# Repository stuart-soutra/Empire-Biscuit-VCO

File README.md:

# Empire Biscuit Voltage Controlled Oscillator
## Details
The Empire Biscuit VCO is a Eurorack Compatible 16HP module implementation of Thomas Henry's VCO design (details available here: https://www.birthofasynth.com/Thomas_Henry/Pages/VCO-1.html).
The module is a single-voice VCO with inputs for CV, Hard Sync, Exp FM, Lin FM and PWM, and sine, triangle, ramp and square wave signal outputs.
The module has controls for Fine and coarse frequency control, FM attenuation and pulse width.
## Transistor Temperature Control
Because of the temperature sensitivity of the PNP transistors (Q1 and Q2) used in the voltage-to-current convertor circuit, it is imperative that these two transistors are thermally matched as closely as possible. For this reason, I have located them as closely together as possible.
When mounting these transistors, I suggest that you apply a small amount of thermal paste between the flat signifier sides of each transistors case, then encase them in epoxy resin (and maybe cover them up with heatshrink to go full belts and braces).
## Front Panel and Mechanical Design
I have included my design of the front panel of the Empire Biscuit ("Empire-Biscuit_PANEL-DESIGN_V1.svg"), that shows mounting hole location and the graphical design - feel free to use this fully or as a drilling template (these are all in .svg format - I recommend using Inkscape to open and edit these).

I constructed the front panel out of aluminium sheet with the following specifications:
- Sheet thickness = 2mm
- Width = 80.9mm (16HP)
- Height = 128mm (Eurorack standard)

The design shows lines for the width of the (recommended) slots at each corner of the module. The end points of these line correspond to the external radius points of each slot. I went with a slot drill size of M2.5.

Other clearance hole sizes:
- Input/Output Receptacles = 8mm
- Pots = 6mm
## Current Rev (Uploaded)
Rev A
## Mods Required After Rev A Testing
As I have not yet completed the changes for Rev B, please implement the following mods if you would like to build it to (fully working) Rev B specifications:
- +12V and -12V should be swapped around at the IDC header - I accidentally mirrored the main input voltages from the power supply, so please make sure that these are the correct way around!
- All 3/4" jacks (input and output) require new connections - Pin 1 (shield) should be connected to GND, and Pin 2 should be the respective positive connection for each. The use of TRRS receptacles for mono connections caused some confusion here.
- For all potentionmeters, swap connections to pin 1 amd 3 around so that each control increases with clockwise rotation instead of decreasing.

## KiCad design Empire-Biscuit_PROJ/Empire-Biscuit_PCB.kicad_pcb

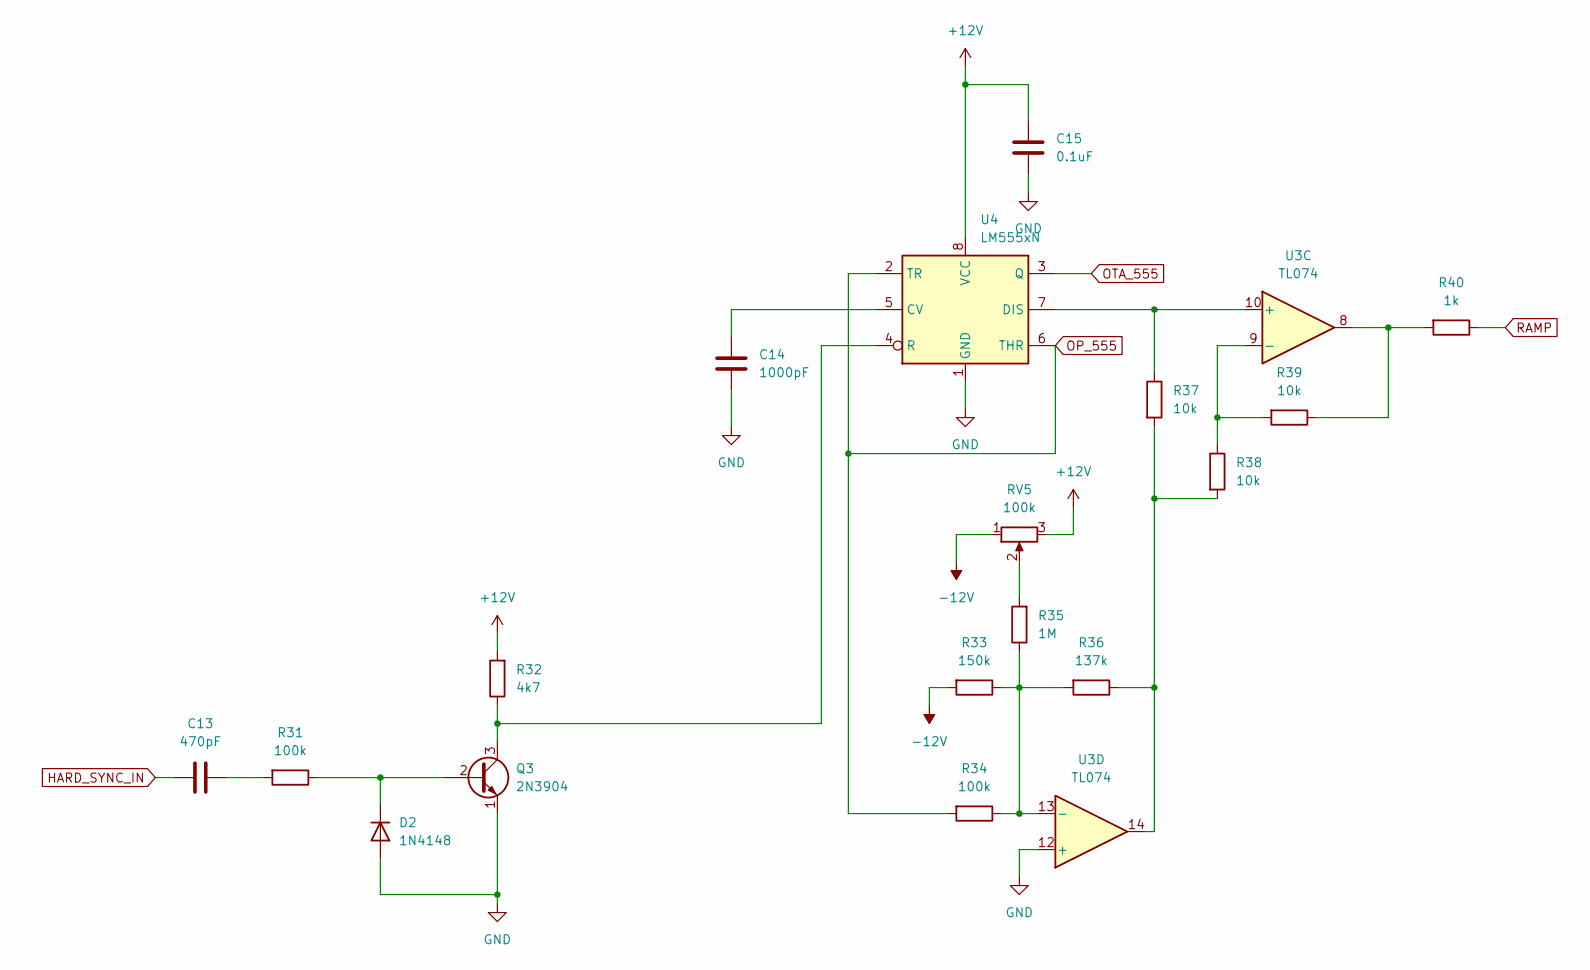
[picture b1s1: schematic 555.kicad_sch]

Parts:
C13: 470pF; C_0805_2012Metric_Pad1.18x1.45mm_HandSolder
C14: 1000pF; C_0805_2012Metric_Pad1.18x1.45mm_HandSolder
C15: 0.1uF; C_0805_2012Metric_Pad1.18x1.45mm_HandSolder
D2: 1N4148; D_DO-35_SOD27_P7.62mm_Horizontal
Q3: 2N3904; TO-92_Inline
R31, R34: 100k; R_0805_2012Metric_Pad1.20x1.40mm_HandSolder
R32: 4k7; R_0805_2012Metric_Pad1.20x1.40mm_HandSolder
R33: 150k; R_0805_2012Metric_Pad1.20x1.40mm_HandSolder
R35: 1M; R_0805_2012Metric_Pad1.20x1.40mm_HandSolder
R36: 137k; R_0805_2012Metric_Pad1.20x1.40mm_HandSolder
R37, R38, R39: 10k; R_0805_2012Metric_Pad1.20x1.40mm_HandSolder
R40: 1k; R_0805_2012Metric_Pad1.20x1.40mm_HandSolder
RV5: 100k; Potentiometer_Vishay_T73XW_Horizontal
U3: TL074
U4: LM555xN; DIP-8_W7.62mm

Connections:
+12V: C15.2, R32.2, RV5.3, U4.8 (VCC); also elsewhere on the board
-12V: R33.2, RV5.1; also elsewhere on the board
GND: C14.1, C15.1, D2.2 (A), Q3.1 (E), U3.12 (+), U4.1 (GND); also elsewhere on the board
HARD_SYNC_IN: C13.2; also elsewhere on the board
unnamed: C13.1, R31.2
unnamed: C14.2, U4.5 (CV)
unnamed: D2.1 (K), Q3.2 (B), R31.1
unnamed: Q3.3 (C), R32.1, U4.4 (R)
unnamed: R33.1, R34.1, R35.1, R36.2, U3.13 (-)
unnamed: R35.2, RV5.2
unnamed: R36.1, R37.2, R38.2, U3.14
unnamed: R37.1, U3.10 (+), U4.7 (DIS)
unnamed: R38.1, R39.2, U3.9 (-)
unnamed: R39.1, R40.2, U3.8
OP_555: R34.2, U4.2 (TR), U4.6 (THR); also elsewhere on the board
OTA_555: U4.3 (Q); also elsewhere on the board
RAMP: R40.1; also elsewhere on the board

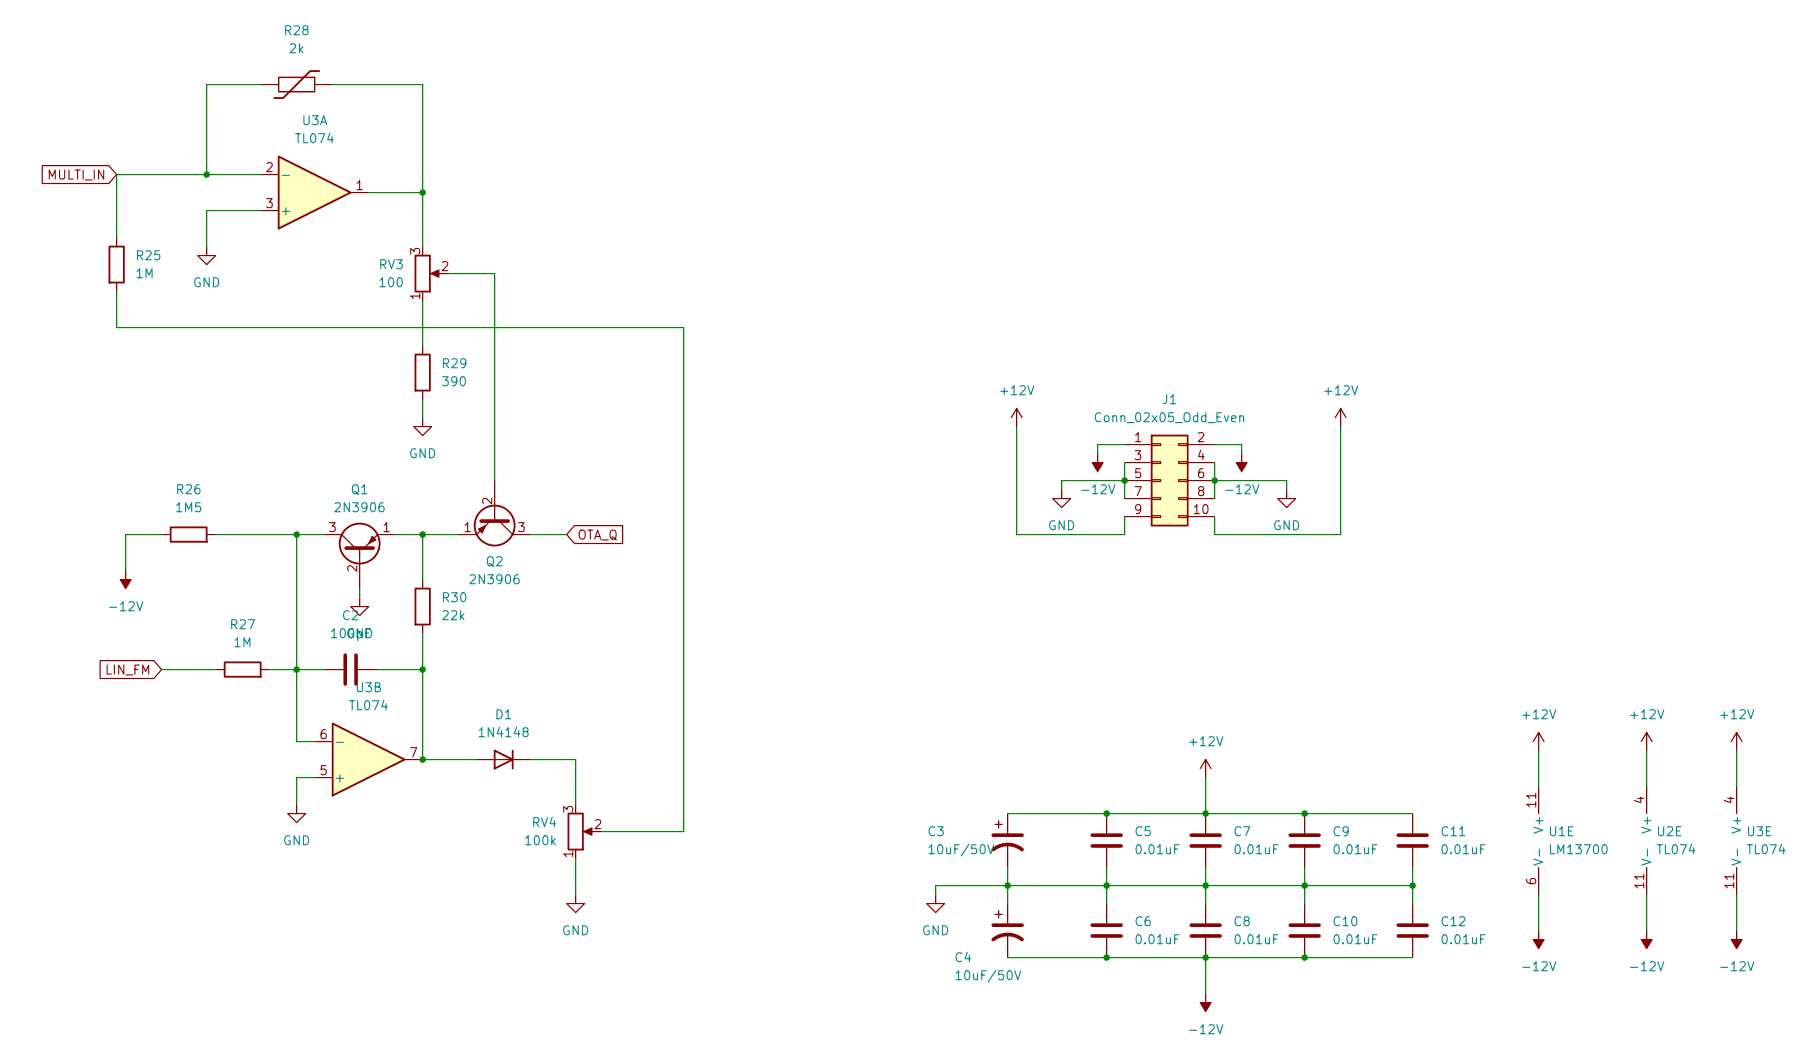
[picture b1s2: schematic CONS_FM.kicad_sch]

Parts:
C2: 100pF; C_0805_2012Metric_Pad1.18x1.45mm_HandSolder
C3, C4: 10uF/50V; CP_Radial_D5.0mm_P2.00mm
C5, C6, C7, C8, C9, C10, C11, C12: 0.01uF; C_0805_2012Metric_Pad1.18x1.45mm_HandSolder
D1: 1N4148; D_DO-35_SOD27_P7.62mm_Horizontal
J1: Conn_02x05_Odd_Even; PinHeader_2x05_P2.54mm_Vertical
Q1, Q2: 2N3906; TO-92_Inline
R25, R27: 1M; R_0805_2012Metric_Pad1.20x1.40mm_HandSolder
R26: 1M5; R_0805_2012Metric_Pad1.20x1.40mm_HandSolder
R28: 2k; R_Axial_DIN0204_L3.6mm_D1.6mm_P2.54mm_Vertical
R29: 390; R_0805_2012Metric_Pad1.20x1.40mm_HandSolder
R30: 22k; R_0805_2012Metric_Pad1.20x1.40mm_HandSolder
RV3: 100; Potentiometer_Vishay_T73XW_Horizontal
RV4: 100k; Potentiometer_Vishay_T73XW_Horizontal
U1: LM13700; SOIC-16_3.9x9.9mm_P1.27mm
U2: TL074; DIP-14_W7.62mm_Socket_LongPads
U3: TL074

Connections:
+12V: C3.1, C5.2, C7.2, C9.2, C11.2, J1.9, J1.10, U1.11 (V+), U2.4 (V+), U3.4 (V+); also elsewhere on the board
-12V: C4.2, C6.1, C8.1, C10.1, C12.1, J1.1, J1.2, R26.1, U1.6 (V-), U2.11 (V-), U3.11 (V-); also elsewhere on the board
GND: C3.2, C4.1, C5.1, C6.2, C7.1, C8.2, C9.1, C10.2, C11.1, C12.2, J1.3, J1.4, J1.5, J1.6, J1.7, J1.8, Q1.2 (B), R29.2, RV4.1, U3.3 (+), U3.5 (+); also elsewhere on the board
LIN_FM: R27.1; also elsewhere on the board
MULTI_IN: R25.1, R28.2, U3.2 (-); also elsewhere on the board
unnamed: C2.1, Q1.3 (C), R26.2, R27.2, U3.6 (-)
unnamed: C2.2, D1.2 (A), R30.2, U3.7
unnamed: D1.1 (K), RV4.3
unnamed: Q1.1 (E), Q2.1 (E), R30.1
unnamed: Q2.2 (B), RV3.2
unnamed: R25.2, RV4.2
unnamed: R28.1, RV3.3, U3.1
unnamed: R29.1, RV3.1
OTA_Q: Q2.3 (C); also elsewhere on the board

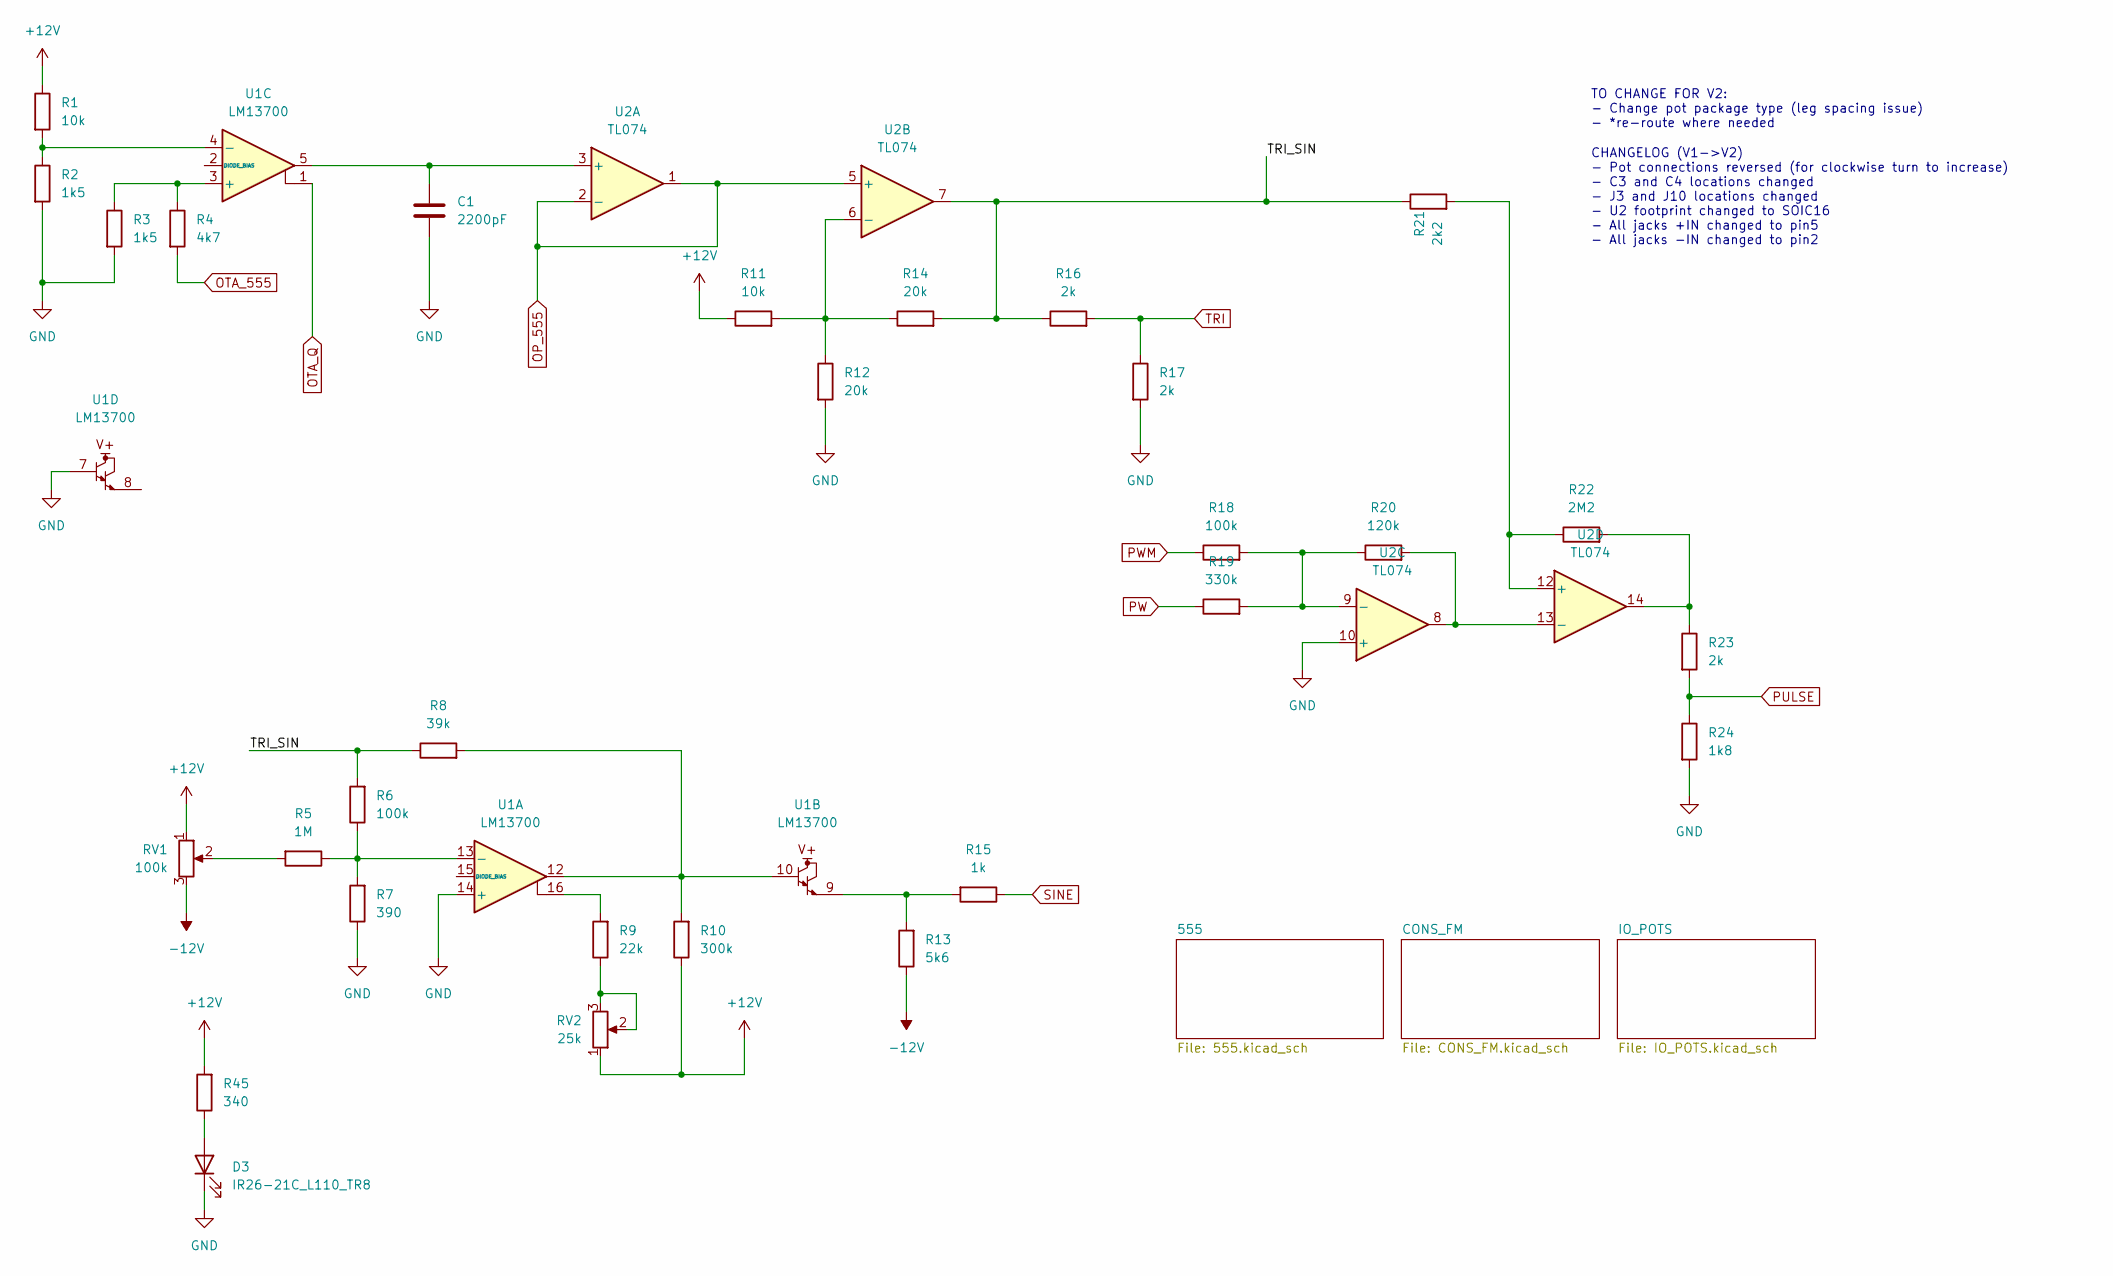
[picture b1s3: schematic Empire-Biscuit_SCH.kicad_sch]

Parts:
C1: 2200pF; C_0805_2012Metric_Pad1.18x1.45mm_HandSolder
D3: IR26-21C_L110_TR8; LED_1206_3216Metric
R1, R11: 10k; R_0805_2012Metric_Pad1.20x1.40mm_HandSolder
R2, R3: 1k5; R_0805_2012Metric_Pad1.20x1.40mm_HandSolder
R4: 4k7; R_0805_2012Metric_Pad1.20x1.40mm_HandSolder
R5: 1M; R_0805_2012Metric_Pad1.20x1.40mm_HandSolder
R6, R18: 100k; R_0805_2012Metric_Pad1.20x1.40mm_HandSolder
R7: 390; R_0805_2012Metric_Pad1.20x1.40mm_HandSolder
R8: 39k; R_0805_2012Metric_Pad1.20x1.40mm_HandSolder
R9: 22k; R_0805_2012Metric_Pad1.20x1.40mm_HandSolder
R10: 300k; R_0805_2012Metric_Pad1.20x1.40mm_HandSolder
R12, R14: 20k; R_0805_2012Metric_Pad1.20x1.40mm_HandSolder
R13: 5k6; R_0805_2012Metric_Pad1.20x1.40mm_HandSolder
R15: 1k; R_0805_2012Metric_Pad1.20x1.40mm_HandSolder
R16, R17, R23: 2k; R_0805_2012Metric_Pad1.20x1.40mm_HandSolder
R19: 330k; R_0805_2012Metric_Pad1.20x1.40mm_HandSolder
R20: 120k; R_0805_2012Metric_Pad1.20x1.40mm_HandSolder
R21: 2k2; R_0805_2012Metric_Pad1.20x1.40mm_HandSolder
R22: 2M2; R_0805_2012Metric_Pad1.20x1.40mm_HandSolder
R24: 1k8; R_0805_2012Metric_Pad1.20x1.40mm_HandSolder
R45: 340; R_0805_2012Metric_Pad1.20x1.40mm_HandSolder
RV1: 100k; Potentiometer_Vishay_T73XW_Horizontal
RV2: 25k; Potentiometer_Vishay_T73XW_Horizontal
U1: LM13700; SOIC-16_3.9x9.9mm_P1.27mm
U2: TL074; DIP-14_W7.62mm_Socket_LongPads

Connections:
+12V: R1.1, R10.1, R11.1, R45.2, RV1.1, RV2.1; also elsewhere on the board
-12V: R13.1, RV1.3; also elsewhere on the board
/TRI_SIN: R6.2, R8.1, R14.2, R16.1, R21.1, U2.7
GND: C1.2, D3.1 (K), R2.2, R3.2, R7.1, R12.2, R17.2, R24.2, U1.7, U1.14 (+), U2.10 (+); also elsewhere on the board
unnamed: C1.1, U1.5, U2.3 (+)
unnamed: D3.2 (A), R45.1
unnamed: R1.2, R2.1, U1.4 (-)
unnamed: R3.1, R4.1, U1.3 (+)
unnamed: R5.1, R6.1, R7.2, U1.13 (-)
unnamed: R5.2, RV1.2
unnamed: R9.1, RV2.2, RV2.3
unnamed: R9.2, U1.16
unnamed: R8.2, R10.2, U1.10, U1.12
unnamed: R11.2, R12.1, R14.1, U2.6 (-)
unnamed: R13.2, R15.2, U1.9
unnamed: R18.2, R19.2, R20.1, U2.9 (-)
unnamed: R20.2, U2.8, U2.13 (-)
unnamed: R21.2, R22.1, U2.12 (+)
unnamed: R22.2, R23.1, U2.14
OP_555: U2.1, U2.2 (-), U2.5 (+); also elsewhere on the board
OTA_555: R4.2; also elsewhere on the board
OTA_Q: U1.1; also elsewhere on the board
PULSE: R23.2, R24.1; also elsewhere on the board
PW: R19.1; also elsewhere on the board
PWM: R18.1; also elsewhere on the board
SINE: R15.1; also elsewhere on the board
TRI: R16.2, R17.1; also elsewhere on the board

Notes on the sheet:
CHANGELOG (V1->V2) - Pot connections reversed (for clockwise turn to increase) - C3 and C4 locations changed - J3 and J10 locations changed - U2 footprint changed to SOIC16 - All jacks +IN changed to pin5 - All jacks -IN changed to pin2
TO CHANGE FOR V2: - Change pot package type (leg spacing issue) - *re-route where needed

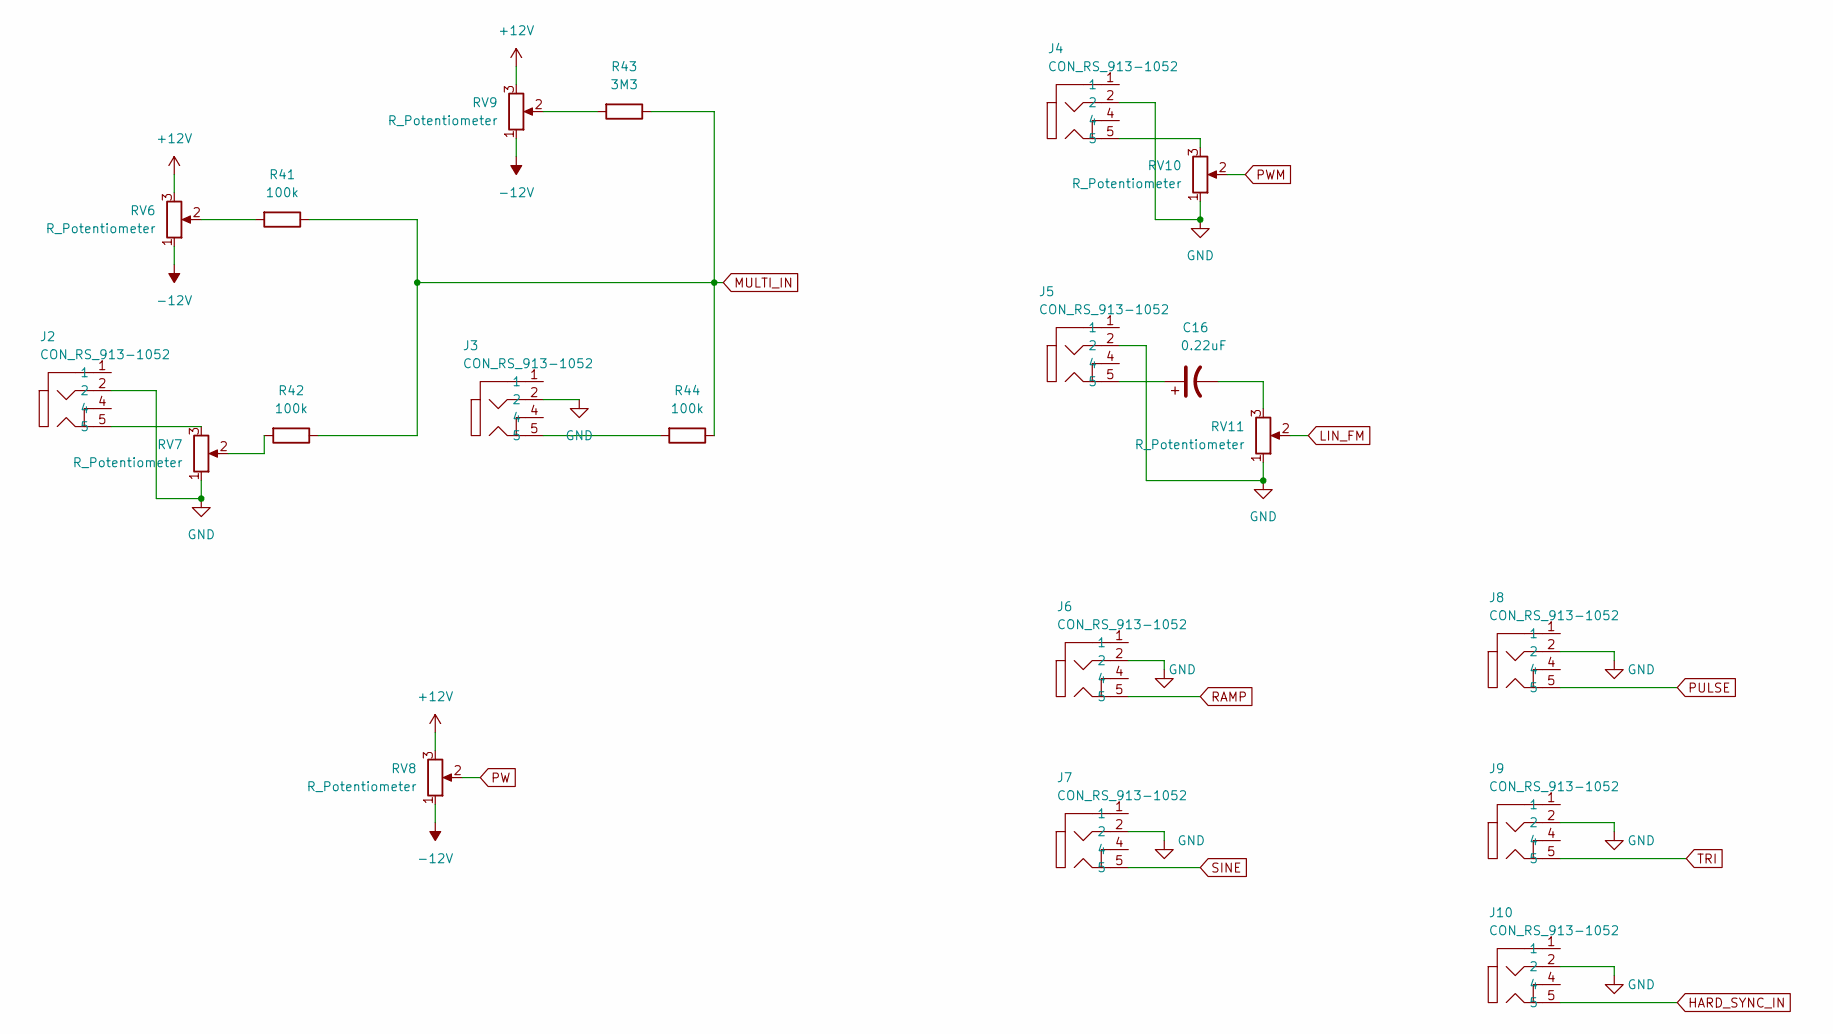
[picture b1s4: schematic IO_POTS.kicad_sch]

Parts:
C16: 0.22uF; CP_Radial_D5.0mm_P2.00mm
J2, J3, J4, J5, J6, J7, J8, J9, J10: CON_RS_913-1052
R41, R42, R44: 100k; R_0805_2012Metric_Pad1.20x1.40mm_HandSolder
R43: 3M3; R_0805_2012Metric_Pad1.20x1.40mm_HandSolder
RV6, RV7, RV8, RV9, RV10, RV11: R_Potentiometer; Potentiometer_Alps_RK09K_Single_Vertical

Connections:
+12V: RV6.3, RV8.3, RV9.3; also elsewhere on the board
-12V: RV6.1, RV8.1, RV9.1; also elsewhere on the board
GND: J2.2, J3.2, J4.2, J5.2, J6.2, J7.2, J8.2, J9.2, J10.2, RV7.1, RV10.1, RV11.1; also elsewhere on the board
HARD_SYNC_IN: J10.5; also elsewhere on the board
LIN_FM: RV11.2; also elsewhere on the board
MULTI_IN: R41.1, R42.1, R43.1, R44.1; also elsewhere on the board
unnamed: C16.1, J5.5
unnamed: C16.2, RV11.3
unnamed: J2.5, RV7.3
unnamed: J3.5, R44.2
unnamed: J4.5, RV10.3
unnamed: R41.2, RV6.2
unnamed: R42.2, RV7.2
unnamed: R43.2, RV9.2
PULSE: J8.5; also elsewhere on the board
PW: RV8.2; also elsewhere on the board
PWM: RV10.2; also elsewhere on the board
RAMP: J6.5; also elsewhere on the board
SINE: J7.5; also elsewhere on the board
TRI: J9.5; also elsewhere on the board

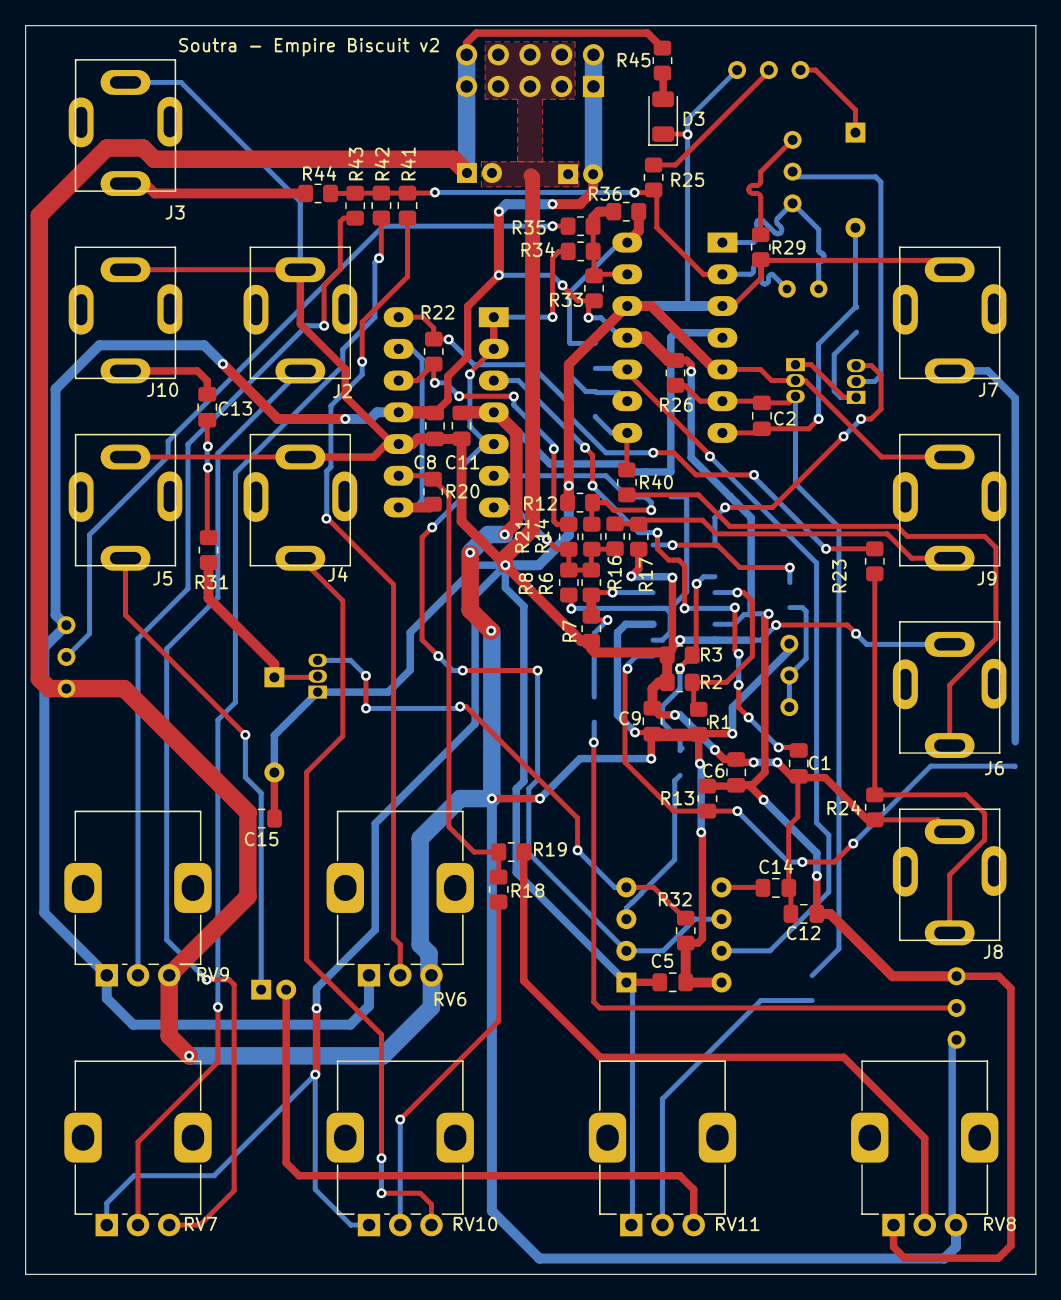
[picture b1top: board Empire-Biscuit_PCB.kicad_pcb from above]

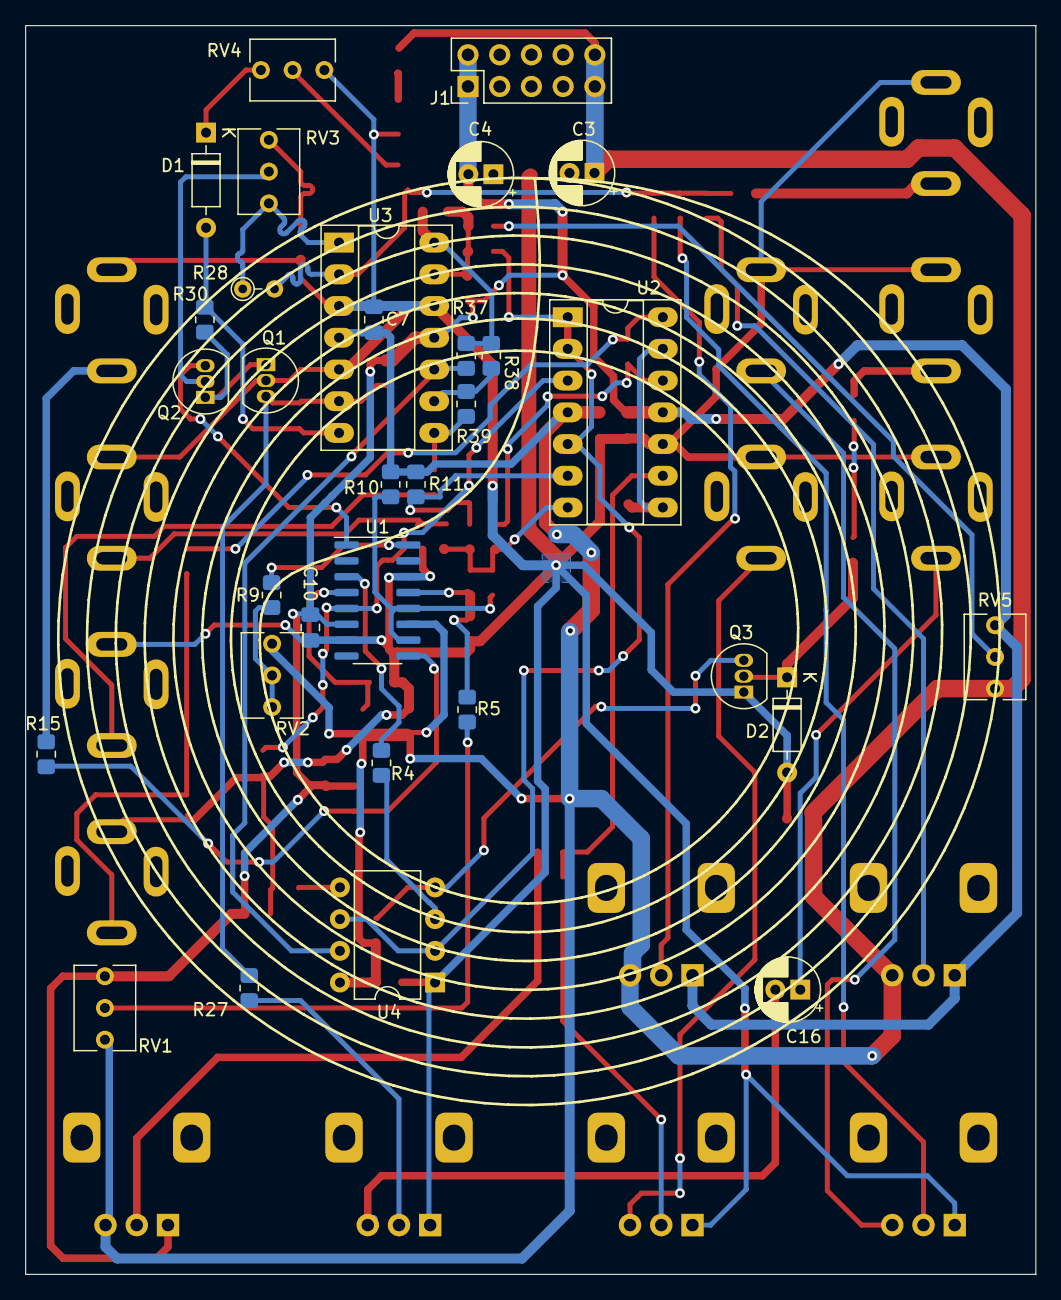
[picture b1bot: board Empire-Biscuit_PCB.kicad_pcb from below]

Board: 2 copper layers, 80.9 x 100.0 mm, 92 parts (32 on the bottom side), 57 nets.

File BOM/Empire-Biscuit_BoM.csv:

"Id";"Designator";"Footprint";"Quantity";"Designation";"Supplier and ref";
1;"RV10,RV6,RV9,RV8,RV7,RV11";"Potentiometer_Alps_RK09K_Single_Vertical";6;"R_Potentiometer";;;
2;"R29,R7";"R_0805_2012Metric_Pad1.20x1.40mm_HandSolder";2;"390";;;
3;"J10,J2,J8,J9,J3,J5,J7,J4,J6";"CON_RS_913-1052";9;"CON_RS_913-1052";;;
4;"R19";"R_0805_2012Metric_Pad1.20x1.40mm_HandSolder";1;"330k";;;
5;"R31,R6,R42,R44,R41,R34,R18";"R_0805_2012Metric_Pad1.20x1.40mm_HandSolder";7;"100k";;;
6;"R45";"R_0805_2012Metric_Pad1.20x1.40mm_HandSolder";1;"340";;;
7;"R13";"R_0805_2012Metric_Pad1.20x1.40mm_HandSolder";1;"5k6";;;
8;"R22";"R_0805_2012Metric_Pad1.20x1.40mm_HandSolder";1;"2M2";;;
9;"R23,R16,R17";"R_0805_2012Metric_Pad1.20x1.40mm_HandSolder";3;"2k";;;
10;"R8";"R_0805_2012Metric_Pad1.20x1.40mm_HandSolder";1;"39k";;;
11;"C11,C5,C6,C8,C9,C12,C7,C10";"C_0805_2012Metric_Pad1.18x1.45mm_HandSolder";8;"0.01uF";;;
12;"R24";"R_0805_2012Metric_Pad1.20x1.40mm_HandSolder";1;"1k8";;;
13;"R35,R25,R5,R27";"R_0805_2012Metric_Pad1.20x1.40mm_HandSolder";4;"1M";;;
14;"R1,R38,R11,R39,R37";"R_0805_2012Metric_Pad1.20x1.40mm_HandSolder";5;"10k";;;
15;"C2";"C_0805_2012Metric_Pad1.18x1.45mm_HandSolder";1;"100pF";;;
16;"R14,R12";"R_0805_2012Metric_Pad1.20x1.40mm_HandSolder";2;"20k";;;
17;"R20";"R_0805_2012Metric_Pad1.20x1.40mm_HandSolder";1;"120k";;;
18;"R21";"R_0805_2012Metric_Pad1.20x1.40mm_HandSolder";1;"2k2";;;
19;"R33";"R_0805_2012Metric_Pad1.20x1.40mm_HandSolder";1;"150k";;;
20;"R2,R3";"R_0805_2012Metric_Pad1.20x1.40mm_HandSolder";2;"1k5";;;
21;"C14";"C_0805_2012Metric_Pad1.18x1.45mm_HandSolder";1;"1000pF";;;
22;"C13";"C_0805_2012Metric_Pad1.18x1.45mm_HandSolder";1;"470pF";;;
23;"R40,R15";"R_0805_2012Metric_Pad1.20x1.40mm_HandSolder";2;"1k";;;
24;"C1";"C_0805_2012Metric_Pad1.18x1.45mm_HandSolder";1;"2200pF";;;
25;"C15";"C_0805_2012Metric_Pad1.18x1.45mm_HandSolder";1;"0.1uF";;;
26;"R26";"R_0805_2012Metric_Pad1.20x1.40mm_HandSolder";1;"1M5";;;
27;"R32,R4";"R_0805_2012Metric_Pad1.20x1.40mm_HandSolder";2;"4k7";;;
28;"D3";"LED_1206_3216Metric";1;"IR26-21C_L110_TR8";;;
29;"R36";"R_0805_2012Metric_Pad1.20x1.40mm_HandSolder";1;"137k";;;
30;"R43";"R_0805_2012Metric_Pad1.20x1.40mm_HandSolder";1;"3M3";;;
31;"U2,U3";"DIP-14_W7.62mm_Socket_LongPads";2;"TL074";;;
32;"RV1,RV4,RV5";"Potentiometer_Vishay_T73XW_Horizontal";3;"100k";;;
33;"D2,D1";"D_DO-35_SOD27_P7.62mm_Horizontal";2;"1N4148";;;
34;"R30,R9";"R_0805_2012Metric_Pad1.20x1.40mm_HandSolder";2;"22k";;;
35;"U4";"DIP-8_W7.62mm";1;"LM555xN";;;
36;"RV2";"Potentiometer_Vishay_T73XW_Horizontal";1;"25k";;;
37;"C16";"CP_Radial_D5.0mm_P2.00mm";1;"0.22uF";;;
38;"R28";"R_Axial_DIN0204_L3.6mm_D1.6mm_P2.54mm_Vertical";1;"2k";;;
39;"J1";"PinHeader_2x05_P2.54mm_Vertical";1;"Conn_02x05_Odd_Even";;;
40;"Q2,Q1";"TO-92_Inline";2;"2N3906";;;
41;"RV3";"Potentiometer_Vishay_T73XW_Horizontal";1;"100";;;
42;"R10";"R_0805_2012Metric_Pad1.20x1.40mm_HandSolder";1;"300k";;;
43;"U1";"SOIC-16_3.9x9.9mm_P1.27mm";1;"LM13700";;;
44;"C3,C4";"CP_Radial_D5.0mm_P2.00mm";2;"10uF/50V";;;
45;"Q3";"TO-92_Inline";1;"2N3904";;;
